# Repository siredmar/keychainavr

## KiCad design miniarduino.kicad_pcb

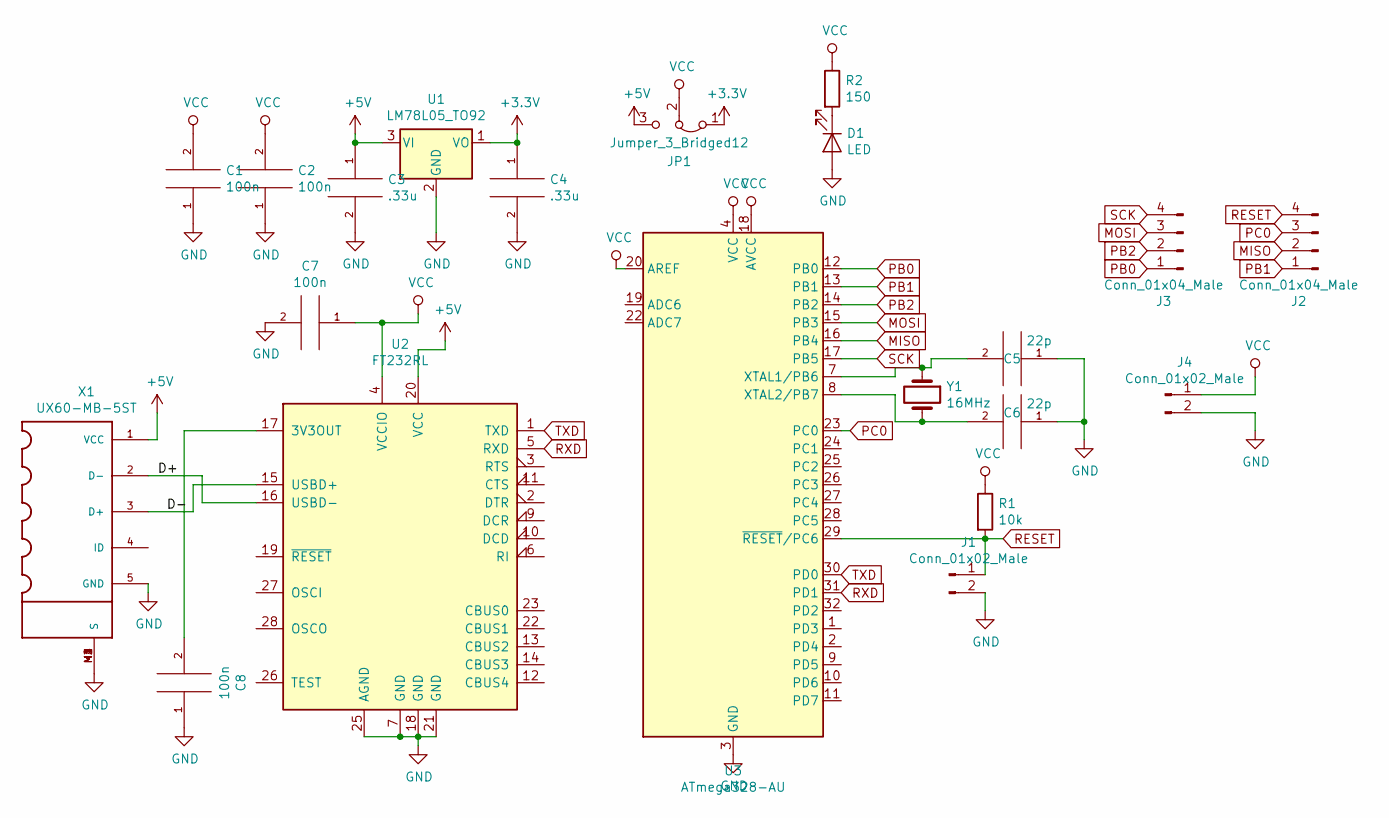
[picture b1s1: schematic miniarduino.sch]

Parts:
C1, C2, C7, C8: 100n; C_0603_1608Metric_Pad1.05x0.95mm_HandSolder
C3, C4: .33u; C_0805_2012Metric_Pad1.15x1.40mm_HandSolder
C5, C6: 22p; C_0603_1608Metric_Pad1.05x0.95mm_HandSolder
D1: LED; LED_0805_2012Metric_Pad1.15x1.40mm_HandSolder
J1, J4: Conn_01x02_Male; PinHeader_1x02_P2.54mm_Vertical
J2, J3: Conn_01x04_Male; PinHeader_1x04_P2.54mm_Vertical
JP1: Jumper_3_Bridged12; PinHeader_1x03_P2.54mm_Vertical
R1: 10k; R_0603_1608Metric_Pad1.05x0.95mm_HandSolder
R2: 150; R_0603_1608Metric_Pad1.05x0.95mm_HandSolder
U1: LM78L05_TO92; SOT-223-3_TabPin2
U2: FT232RL; SSOP-28_5.3x10.2mm_P0.65mm
U3: ATmega328-AU; TQFP-32_7x7mm_P0.8mm
X1: UX60-MB-5ST; UX60SC-MB-5ST
Y1: 16MHz; Crystal_SMD_7050-2Pin_7.0x5.0mm_HandSoldering

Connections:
+3V3: C4.1, JP1.1 (A), U1.1 (VO)
+5V: C3.1, JP1.3 (B), U1.3 (VI), U2.20 (VCC), X1.1 (VCC)
/D+: U2.16 (USBD-), X1.2 (D-)
/D-: U2.15 (USBD+), X1.3 (D+)
/led: D1.1 (K), R2.2
GND: C1.1, C2.1, C3.2, C4.2, C5.1, C6.1, C7.2, C8.1, D1.2 (A), J1.2, J4.2, U1.2 (GND), U2.7 (GND), U2.18 (GND), U2.21 (GND), U2.25 (AGND), U3.3 (GND), U3.5 (GND), U3.21 (GND), X1.5 (GND), X1.M1 (S), X1.M2 (S), X1.M3 (S), X1.M4 (S)
MISO: J2.2, U3.16 (PB4)
MOSI: J3.3, U3.15 (PB3)
unnamed: C5.2, U3.7 (XTAL1/PB6), Y1.1
unnamed: C6.2, U3.8 (XTAL2/PB7), Y1.2
unnamed: C8.2, U2.17 (3V3OUT)
PB0: J3.1, U3.12 (PB0)
PB1: J2.1, U3.13 (PB1)
PB2: J3.2, U3.14 (PB2)
PC0: J2.3, U3.23 (PC0)
RESET: J1.1, J2.4, R1.2, U3.29 (~RESET~/PC6)
RXD: U2.5 (RXD), U3.31 (PD1)
SCK: J3.4, U3.17 (PB5)
TXD: U2.1 (TXD), U3.30 (PD0)
VCC: C1.2, C2.2, C7.1, J4.1, JP1.2 (C), R1.1, R2.1, U2.4 (VCCIO), U3.4 (VCC), U3.6 (VCC), U3.18 (AVCC), U3.20 (AREF)

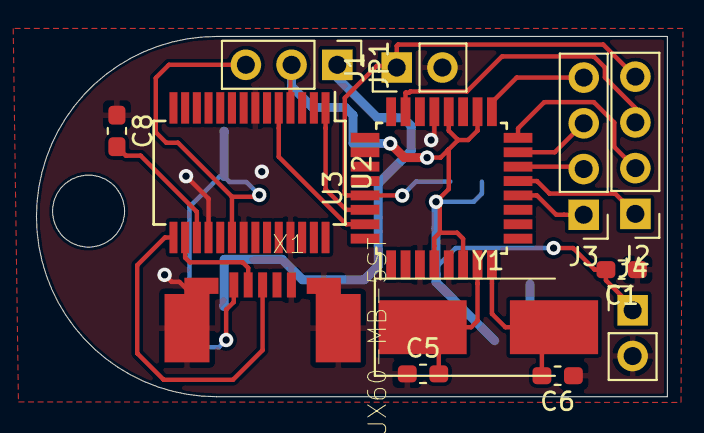
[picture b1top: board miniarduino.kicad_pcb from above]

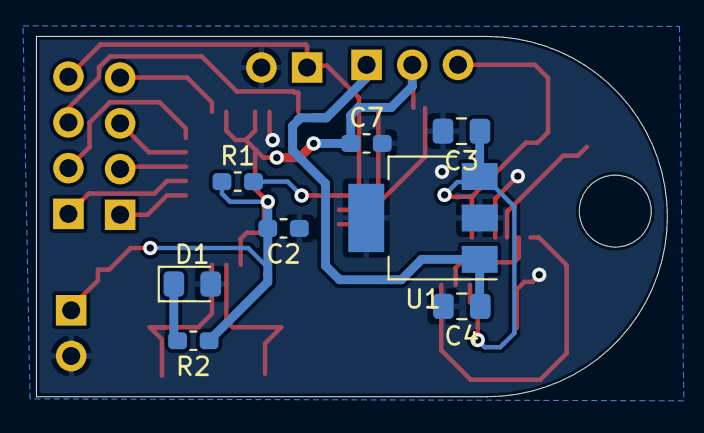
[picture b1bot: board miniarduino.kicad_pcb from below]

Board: 2 copper layers, 35.1 x 20.0 mm, 21 parts (8 on the bottom side), 20 nets.

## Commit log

2019-11-11 Added first version of pcb
